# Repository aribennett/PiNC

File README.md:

# PiNC
Open Source Raspberry Pi CNC Control Hardware

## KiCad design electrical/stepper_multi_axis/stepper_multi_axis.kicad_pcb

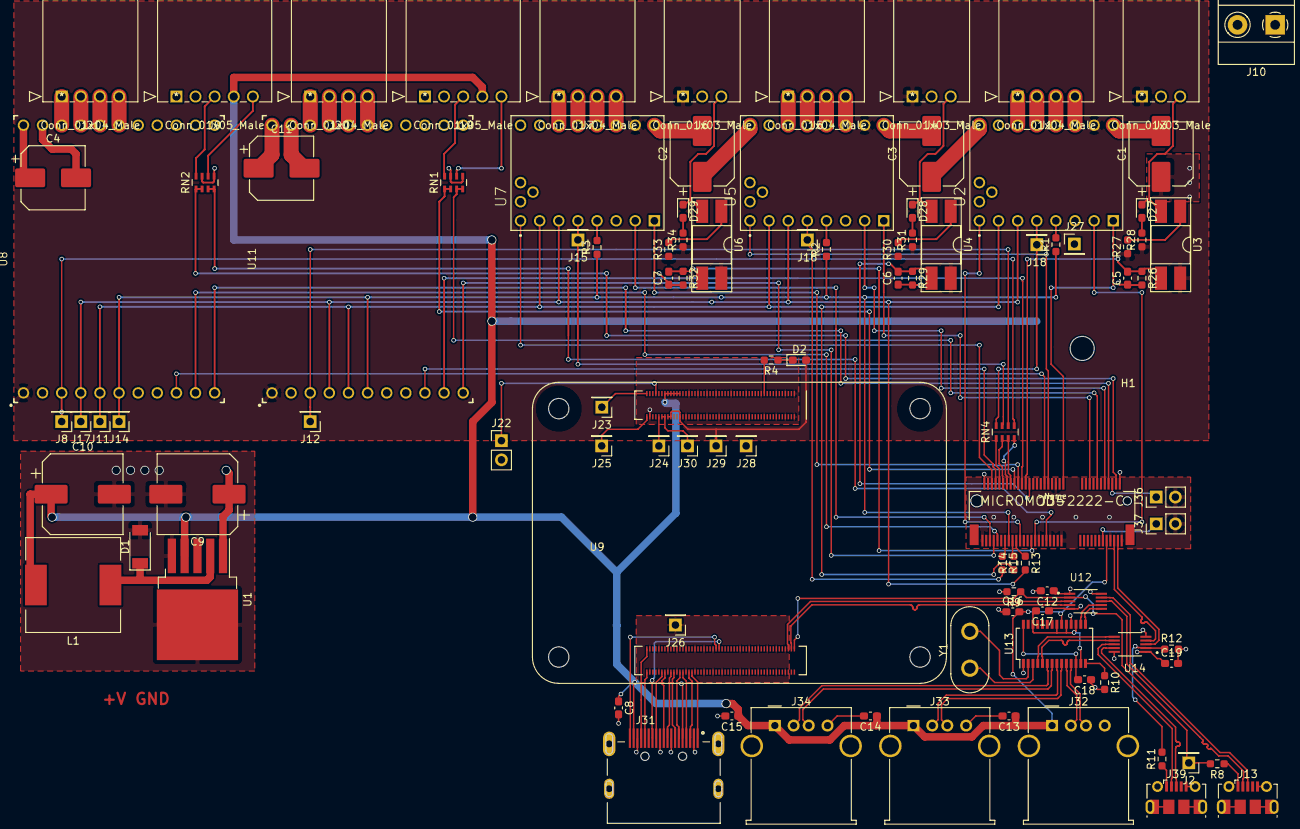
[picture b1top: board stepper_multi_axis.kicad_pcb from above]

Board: 4 copper layers, 102 parts (0 on the bottom side), 126 nets.

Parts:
C1, C2, C3, C4, C11: 10uF; CP_Elec_8x6.7
C5, C6, C7, C8, C12, C13, C14, C15, C19: 100nF; C_0603_1608Metric_Pad1.08x0.95mm_HandSolder
C9: 100uF; CP_Elec_10x12.5
C10: 1000uF; CP_Elec_10x12.5
C16, C17, C18: 10uF; C_0603_1608Metric_Pad1.08x0.95mm_HandSolder
D1: D_Schottky; D_SOD-128
D2: LED; D_0603_1608Metric_Pad1.05x0.95mm_HandSolder
D27, D28, D29: LED; LED_0603_1608Metric_Pad1.05x0.95mm_HandSolder
H1: MountingHole; MountingHole_3.2mm_M3
J1, J5, J7, J20, J21: Conn_01x04_Male; 1719740104
J2, J23, J24, J25, J26, J27, J28, J29, J30: Conn_01x01; PinHeader_1x01_P2.54mm_Vertical
J3, J4, J6: Conn_01x03_Male; 1719740103
J8, J11, J12, J14, J15, J16, J17, J18: Conn_01x01_Male; PinHeader_1x01_P2.54mm_Vertical
J9, J19: Conn_01x05_Male; 1719740105
J10: Conn_01x02_Male; TerminalBlock_Phoenix_MKDS-1,5-2_1x02_P5.00mm_Horizontal
J13, J39: USB_B_Micro; USB_Micro-B_Molex-105017-0001
J22, J36, J37: Conn_01x02_Male; PinHeader_1x02_P2.54mm_Vertical
J31: HDMI_A_1.4; TE_1827059-3
J32, J33, J34: USB_A; USB_A_Molex_67643_Horizontal
J35: MICROMOD-2222-C; M.2-CONNECTOR-E
L1: 100uH; L_12x12mm_H8mm
R1, R2, R3, R13, R14, R15, R26, R27, R28, R29, R30, R31, R32, R33, R34: 100; R_0603_1608Metric_Pad0.98x0.95mm_HandSolder
R4: 1k; R_0603_1608Metric_Pad0.98x0.95mm_HandSolder
R8, R9, R11, R12: 2.2k; R_0603_1608Metric_Pad0.98x0.95mm_HandSolder
R10: 2.7k; R_0603_1608Metric_Pad0.98x0.95mm_HandSolder
RN1, RN2: R_1K_4; R_Array_Concave_4x0603
RN4: R_100_4; R_Array_Concave_4x0603
U1: LM2576S-5; TO-263-5_TabPin3
U2, U5, U7: TMC5160_SILENTSTEPSTICK; MODULE_TMC_SILENTSTEPSTICK
U3, U4, U6: LTV-817; DIP-4_W8.89mm_SMDSocket_LongPads
U8, U11: TMC5160-BOB; 22pin1,5x1,1-BOB
U9: Compute_Module_4_Connectors; Raspberry-Pi-4-Compute-Module
U12, U14: FSUSB42MUX; SOP50P490X110-10N
U13: FE1.1s; SSOP-28_3.9x9.9mm_P0.635mm
Y1: Crystal; Crystal_HC50_Vertical

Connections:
+1V8: J30.1, U9.88, U9.90
+3.3VA: C12.1, C19.1, D2.2, J3.1, J4.1, J6.1, J29.1, J35.2, J35.74, R27.1, R28.1, R30.1, R31.1, R33.1, R34.1, U2.JP2_7, U3.4, U4.4, U5.JP2_7, U6.4, U7.JP2_7, U8.1, U9.78, U9.84, U9.86, U11.1, U12.1, U13.18, U14.1
+5V: C8.1, C10.1, C13.1, C14.1, C15.1, C16.2, J9.4, J19.4, J31.18, J32.1, J33.1, J34.1, J35.9, L1.2, U1.4, U9.77, U9.79, U9.81, U9.83, U9.85, U9.87, U13.20
/CS_A: J12.1, RN4.6, U11.3
/CS_B: J8.1, RN4.5, U8.3
/CS_X: J18.1, RN4.8, U2.JP1_5
/CS_Y: J16.1, R15.2, U5.JP1_5
/CS_Z: J15.1, RN4.7, U7.JP1_5
/D_A: J35.69, U11.11
/D_B: J35.8, U8.11
/ENCA_A: J35.58, RN1.1, RN1.2
/ENCA_B: J35.4, RN2.1, RN2.2
/ENCB_A: J35.14, RN1.3, RN1.4
/ENCB_B: J35.41, RN2.3, RN2.4
/EN_A: J35.68, U11.9
/EN_B: J35.42, U8.9
/LIM_Z: C7.2, J35.49, R32.1, U6.3
/MISO: J14.1, J35.61, R1.1, R2.1, R3.1, U8.6, U11.6
/MOSI: J11.1, R14.1, U2.JP1_7, U5.JP1_7, U7.JP1_7, U8.5, U11.5
/SCK: J17.1, R13.2, U2.JP1_6, U5.JP1_6, U7.JP1_6, U8.4, U11.4
/ST_A: J35.54, U11.10
/ST_B: J35.67, U8.10
/Sheet613FBD85/HDMI0_CEC: J31.13, U9.151
/Sheet613FBD85/HDMI0_CK+: J31.10, U9.188
/Sheet613FBD85/HDMI0_CK-: J31.12, U9.190
/Sheet613FBD85/HDMI0_D0+: J31.7, U9.182
/Sheet613FBD85/HDMI0_D0-: J31.9, U9.184
/Sheet613FBD85/HDMI0_D1+: J31.4, U9.176
/Sheet613FBD85/HDMI0_D1-: J31.6, U9.178
/Sheet613FBD85/HDMI0_D2+: J31.1, U9.170
/Sheet613FBD85/HDMI0_D2-: J31.3, U9.172
/Sheet613FBD85/HDMI0_HOTPLUG: J31.19, U9.153
/Sheet613FBD85/HDMI0_SCL: J31.15, U9.200
/Sheet613FBD85/HDMI0_SDA: J31.16, U9.199
/Sheet613FBD85/USB_N: U9.103, U12.4
/Sheet613FBD85/USB_OTG: J2.1, R8.2, R9.1, U9.101, U12.2
/Sheet613FBD85/USB_P: U9.105, U12.3
/Sheet614CFDB6/1+: J32.3, U13.11
/Sheet614CFDB6/1-: J32.2, U13.10
/Sheet614CFDB6/2+: J33.3, U13.9
/Sheet614CFDB6/2-: J33.2, U13.8
/Sheet614CFDB6/3+: J34.3, U13.7
/Sheet614CFDB6/3-: J34.2, U13.6
/Sheet614CFDB6/INT+: U13.5, U14.7
/Sheet614CFDB6/INT-: U13.4, U14.6
/Sheet614CFDB6/OVERRIDE+: J39.3, U14.9
/Sheet614CFDB6/OVERRIDE-: J39.2, U14.8
/Sheet614CFDB6/PROG+: J13.3, U12.9
/Sheet614CFDB6/PROG-: J13.2, U12.8
/Sheet614CFDB6/USB_A+: U12.7, U13.16
/Sheet614CFDB6/USB_A-: U12.6, U13.15
/Sheet614CFDB6/USB_INTERNAL_N: J35.5, U14.4
/Sheet614CFDB6/USB_INTERNAL_P: J35.3, U14.3
/Stepper_Driver_X/DIR: J35.32, U2.JP1_1
/Stepper_Driver_X/EN: J35.55, U2.JP1_8
/Stepper_Driver_X/Limit: C5.2, J35.52, R26.1, U3.3
/Stepper_Driver_X/STEP: J35.47, U2.JP1_2
/sheet608DFF62/DIR: J35.18, U5.JP1_1
/sheet608DFF62/EN: J35.40, U5.JP1_8
/sheet608DFF62/Limit: C6.2, J35.50, R29.1, U4.3
/sheet608DFF62/STEP: J35.10, U5.JP1_2
/sheet608FE262/DIR: J35.56, U7.JP1_1
/sheet608FE262/EN: J35.70, U7.JP1_8
/sheet608FE262/STEP: J35.71, U7.JP1_2
GND: C1.2, C2.2, C3.2, C4.2, C5.1, C6.1, C7.1, C8.2, C9.2, C10.2, C11.2, C12.2, C13.2, C14.2, C15.2, C16.1, C17.1, C18.1, C19.2, D1.2, J3.2, J4.2, J6.2, J9.1, J10.2, J13.5, J13.6, J19.1, J22.2, J26.1, J27.1, J28.1, J31.2, J31.5, J31.8, J31.11, J31.17, J32.4, J32.5, J33.4, J33.5, J34.4, J34.5, J35.1, J35.7, J35.33, J35.36, J35.39, J35.45, J35.75, J36.2, J37.2, J39.5, J39.6, R9.2, R10.2, R12.2, R26.2, R29.2, R32.2, RN1.5, RN1.7, RN2.5, RN2.7, U1.3, U1.5, U2.JP2_2, U2.JP2_8, U5.JP2_2, U5.JP2_8, U7.JP2_2, U7.JP2_8, U8.2, U8.7, U8.13, U8.18, U9.1, U9.2, U9.7, U9.8, U9.13, U9.14, U9.22, U9.23, U9.32, U9.33, U9.42, U9.43, U9.52, U9.53, U9.59, U9.60, U9.65, U9.66, U9.71, U9.74, U9.98, U9.107, U9.108, U9.113, U9.114, U9.119, U9.120, U9.125, U9.126, U9.131, U9.132, U9.137, U9.138, U9.144, U9.150, U9.155, U9.156, U9.161, U9.162, U9.167, U9.168, U9.173, U9.174, U9.179, U9.180, U9.185, U9.186, U9.191, U9.192, U9.197, U9.198, U11.2, U11.7, U11.13, U11.18, U12.5, U12.10, U13.1, U14.5, U14.10
unnamed: C17.2, U13.13, U13.17, U13.19, U13.21, U13.26
unnamed: C18.2, U13.12, U13.28
unnamed: D1.1, L1.1, U1.2
unnamed: D2.1, R4.1
unnamed: D27.1, J3.3, U3.2
unnamed: D27.2, R28.2
unnamed: D28.1, J4.3, U4.2
unnamed: D28.2, R31.2
unnamed: D29.1, J6.3, U6.2
unnamed: D29.2, R34.2
unnamed: J1.1, U2.JP2_3
unnamed: J1.2, U2.JP2_4
unnamed: J1.3, U2.JP2_5
unnamed: J1.4, U2.JP2_6
unnamed: J5.1, U5.JP2_3
unnamed: J5.2, U5.JP2_4
unnamed: J5.3, U5.JP2_5
unnamed: J5.4, U5.JP2_6
unnamed: J7.1, U7.JP2_3
unnamed: J7.2, U7.JP2_4
unnamed: J7.3, U7.JP2_5
unnamed: J7.4, U7.JP2_6
unnamed: J9.3, RN2.8
unnamed: J9.5, RN2.6
unnamed: J13.1, R8.1
unnamed: J19.3, RN1.8
unnamed: J19.5, RN1.6
unnamed: J20.1, U11.14
unnamed: J20.2, U11.15
unnamed: J20.3, U11.16
unnamed: J20.4, U11.17
unnamed: J21.1, U8.14
unnamed: J21.2, U8.15
unnamed: J21.3, U8.16
unnamed: J21.4, U8.17
unnamed: J22.1, U9.93
unnamed: J23.1, U9.99
unnamed: J24.1, U9.92
unnamed: J25.1, U9.100
unnamed: J35.6, J36.1
unnamed: J35.11, J37.1
unnamed: J35.57, R13.1
unnamed: J35.59, R14.2
unnamed: J35.60, RN4.3
unnamed: J35.62, RN4.4
unnamed: J35.63, R15.1
unnamed: J35.64, RN4.2
unnamed: J35.66, RN4.1
unnamed: J39.1, R11.1
unnamed: R1.2, U2.JP1_4
unnamed: R2.2, U5.JP1_4
unnamed: R3.2, U7.JP1_4
unnamed: R4.2, U9.21
unnamed: R10.1, U13.14
unnamed: R11.2, R12.1, U14.2
unnamed: R27.2, U3.1
unnamed: R30.2, U4.1
unnamed: R33.2, U6.1
unnamed: U13.2, Y1.2
unnamed: U13.3, Y1.1
VBUS: C1.1, C2.1, C3.1, C4.1, C9.1, C11.1, J10.1, U1.1, U2.JP2_1, U5.JP2_1, U7.JP2_1, U8.12, U11.12

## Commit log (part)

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2021-07-29 added cad and folder structure
2021-08-14 added a bunch of kicad stuff
2021-08-16 initial python interface
2021-08-16 updated gitignore
2021-08-16 initial pass at serial packets!
2021-08-16 it makes circles
2021-08-17 added timing to test on rpi
2021-08-18 functioning 4khz hid link
2021-08-19 herp derp
2021-08-19 different IO
2021-08-20 slowed down hid
2021-08-20 added platform agnostic interface
2021-08-20 weird stagning
2021-08-21 mechanical changes
2021-08-23 added higher current drivers
2021-08-30 shipped things
2021-09-01 changed serial framework
2021-09-01 made some changes?
2021-09-02 moved stuff, updated protocol
2021-09-09 finished turret added servo and pwm
2021-09-10 pre delete thru hole
2021-09-12 trying new stuff
2021-09-12 Xometry order 091221
2021-09-29 bunches of changes
2021-09-29 all motors working
2021-09-29 corrected axzes
2021-10-12 added errors and shit
2021-10-12 added gcode solver
2021-10-13 added enable command
2021-10-13 added enable call
2021-10-13 gcoooode
2021-11-15 extracted config
2021-11-19 wiped out lower derivatives
2021-11-19 adde laser, still working.
2021-11-19 rename, add exposure reconfigure
2021-11-20 added a state machine
2021-11-20 calibrated laser
2021-11-20 running gcode!
2021-11-22 cleaned stages
2021-11-29 changed size, we shall see
2021-11-29 expanded firmware
2021-11-29 added solid bodies
2021-11-29 changed packet size to 128
2021-11-29 added counting
2021-11-29 slowed rapid
2021-12-18 fixed turret
2021-12-18 Initial PlatformIO config
2021-12-18 added second project
2021-12-18 removed old libs
2021-12-18 ported to mac
2021-12-18 added jerk control
2021-12-19 mac turret lives
2021-12-19 turret is mostly complete
2021-12-19 removed debug stuff
2021-12-19 added a board ID to the usb devices
2021-12-19 fixed motor command with board ID
2021-12-20 added single axis project
2021-12-21 added terminals
2021-12-23 more requirements
2021-12-23 killed tracking, added cmdline arg
2021-12-23 print the state
2021-12-23 check if controller is working
2021-12-23 added motor command call
2021-12-24 changed init
2021-12-24 re-enable tracking
2021-12-25 Updated z2
2022-01-03 semi-functioning. going to change the planner
2022-02-04 more sw
2022-02-05 added some path planning, killed homing routine
2022-02-05 moar
2022-02-05 homing reneabled
2022-02-05 back to manual
2022-02-05 working servo
2022-02-06 encoders now
2022-02-06 opped jog rate
2022-02-06 fixed jog rate
2022-02-06 lowered deadband
2022-02-06 removed imshow
2022-02-06 changed moments
2022-02-19 updated fw
2022-02-19 updated rule
2022-02-19 updated rules
2022-02-19 i hate udev logic man
2022-02-19 fixed spelling
2022-02-19 changed to symlink
2022-02-19 swapped rule order
2022-02-19 added path to symlink
2022-02-19 added kernel number!
2022-02-19 working udev, tuned controller
2022-02-19 new robot interface
2022-02-19 added trash
2022-02-19 updated packets
2022-02-19 print all the motors
2022-02-19 fixed indexes
2022-02-19 changed control scheme
2022-02-19 oops
2022-02-19 added proportional control
2022-02-19 added a floor handling case
2022-02-19 fixyfix
2022-02-20 added servo position from encoder
2022-02-20 re-add homing
2022-02-20 added a homing speed
2022-02-20 added stall detection
2022-02-20 added new start
2022-02-20 added a print?
2022-02-20 fix the timeout?
2022-02-20 blargh
2022-02-20 idk man
2022-02-20 her derp
2022-02-20 enabled manualstate
2022-02-20 added safe re-enable
2022-02-20 fixed issue with null pointer death
2022-02-20 kinda borken
2022-02-20 re-enable home
2022-02-20 re-enable logging
2022-02-20 added delay. dont love it
2022-02-20 added longer timeout
2022-02-20 added home thing
2022-02-20 reverse reverse
2022-02-20 homing is back babee
2022-02-20 update home strategy
2022-02-20 pulled down timeout
2022-02-20 testing jerg
2022-02-20 adding jog
2022-02-20 drop to manual
2022-02-21 added z jog?
2022-02-21 different logging
2022-02-21 buggos
2022-02-21 printing nominal
2022-02-21 something broken
2022-02-21 found it ...
2022-02-21 big moves
2022-02-21 trimmed laser file
2022-02-21 fix dabug
2022-02-21 added tracking loop and zhoming
2022-02-21 added home center state
2022-02-21 shwoops
2022-02-21 added second jerg
2022-02-21 fixed?
2022-02-21 added another homing pass
2022-02-21 homing should work again
2022-02-21 test motor 0
2022-02-21 remove homing for hot second
2022-02-21 test second axis
2022-02-21 homing should be fully online
2022-02-21 added fix to homing
2022-02-21 fixed home change prant
2022-02-21 changed home posititions
2022-02-21 move more
2022-02-21 tooooo far
2022-02-26 back to homing
2022-03-01 added adc reporting
2022-03-01 update packet def
2022-03-01 added sensor unpacking
2022-03-01 debug them sensors!
2022-03-01 whee
2022-03-01 added output controlls
2022-03-01 added laser config lets goooo
2022-03-01 added laser on off
2022-03-01 changed initail condition
2022-03-01 added fan
2022-03-01 added blower fan to test
2022-03-01 test hotend
2022-03-06 fannnnns
2022-03-06 added pwm output
2022-03-06 test single gpios
2022-03-06 added pwm
2022-03-06 added software pwm, put back in commands
2022-03-06 fixed init maybe
2022-03-06 revert to hardware pwm. no cycles for software
2022-03-06 added thermistor
2022-03-06 voltages backwards
2022-03-06 oooops
2022-03-06 added temp interp
2022-03-06 needs to be monotonically increasing I guess
2022-03-06 whooooopsity poops
2022-03-06 added closed loop thermals
2022-03-06 added index
2022-03-06 whoops need to packl the packet
2022-03-06 wheeee
2022-03-06 wheeeee
2022-03-06 herp derp derp
2022-03-06 try enable lol
2022-04-03 testing
2022-04-03 wider
2022-04-03 busted mask?
2022-04-03 fix it?
2022-04-03 dimmer?
2022-04-03 back to thermistor
2022-04-19 show laser image
2022-04-19 removed bad debug
2022-05-06 lets jog to 00
2022-05-06 lets see if it works
2022-05-06 removed actual motion
2022-05-06 super low kp
2022-05-06 it werk
2022-05-06 disable vleocit controll
2022-05-06 need to enable motor
2022-05-06 disable traking
2022-05-06 added extruder
2022-05-06 reverse and slow doen extruder
2022-05-06 added thermistor controll
2022-05-06 wheee
2022-05-06 I think that might help?
2022-05-06 disable pcf
2022-05-06 added heating step
2022-05-06 fixed stupid reset
2022-05-06 added homing
2022-05-06 added homing and z
2022-05-06 re-enable laser tracking
2022-05-06 maybe?
2022-05-06 maybe maybe?
2022-05-06 added stop condition
2022-05-06 added fine_zHome
2022-05-06 whoops
2022-05-06 fixed start issue
2022-05-06 adjust home
2022-05-06 wrong way
2022-05-06 finer fine home
2022-05-06 getting there
2022-05-06 lets see
2022-05-06 sign issues
2022-05-06 last try
2022-05-06 mayber?
2022-05-06 slow it all down
2022-05-06 changed temp
2022-05-06 moar power
2022-05-10 just homing
2022-05-10 swapped motor
2022-05-10 wrong direction
2022-05-10 added abs stall detection
2022-05-10 why busted
2022-05-10 added print
2022-05-10 maybe fixed?
2022-05-10 welp
2022-05-10 fixed
2022-05-10 shwoop
2022-05-10 fixed scale issue
2022-05-10 change units?
2022-05-10 busted?
2022-05-10 blep
2022-05-10 fixed inversion
2022-05-10 ecentuaLL
2022-05-10 ALL together now
2022-05-10 new gcode
2022-05-10 fixed eof error
2022-05-10 missed subscript
2022-05-10 fixed gcode boog
2022-05-10 minor tweak
2022-05-10 fix edge condition
2022-05-10 welp lets gooo
2022-05-10 added bed on off
2022-05-11 added second thermistor
2022-05-11 maybe table bad?
2022-05-13 turret complete
2022-05-14 finished turret
2022-05-20 removed some files
2022-05-27 lets goooo
2022-05-28 changed gcode
2022-05-28 we'll seeeee
2022-05-29 fix nots
2022-05-29 claener
2022-05-29 cleanup!
2022-06-01 make laser tracking thresh higher
2022-06-02 added test gcode
2022-06-02 blargh need to fix the laser shit
2022-06-02 why u busted
2022-06-02 added benchy
2022-06-02 unstable yo
2022-06-02 slowly increase kp
2022-06-02 huzzah
2022-06-02 why bust
2022-06-02 tweak adn tune
2022-06-02 better pls
2022-06-02 darn
2022-06-02 mabe
2022-06-02 slowdown
2022-06-02 ugh freaking corexy
2022-06-02 blergh
2022-06-02 fix transform
2022-06-02 better debug
2022-06-02 start sloooo
2022-06-02 why u go unstable
2022-06-02 lets gooo
2022-06-06 change to monochrom
2022-06-06 filter
2022-06-06 added depth
2022-06-06 added file writing
2022-06-06 freaking busted
2022-06-06 I wish this worked better
2022-06-06 im dum
2022-06-06 grayscale
2022-06-06 remove non-red channels
2022-06-06 filteeeer
2022-06-06 print out red
2022-06-06 filter better
2022-06-06 whoosp
2022-06-06 more sate
2022-06-06 why does this suk
2022-06-06 higher threhold
2022-06-06 why u suk
2022-06-06 lower thresh
2022-06-06 dumb
2022-06-06 whyyy
2022-06-06 i think I am an idiot
2022-06-06 dunno why
2022-06-06 tunez
2022-06-06 tune z
2022-06-06 added sphere
2022-06-08 brighter laser
2022-06-08 better Z
2022-06-08 lets do a benchy!
2022-06-08 fix z
2022-06-08 hmmm
2022-06-26 added print debug
2022-06-26 changed packet to make faster
2022-06-26 does it work?
2022-06-26 whheee
2022-06-26 disable nominal z
2022-06-26 revert
2022-06-26 added blower and different gcode
2022-06-26 added cooling fan
2022-06-26 added turning on cooling fan later
2022-07-04 okay maybe dis work
2022-07-05 added minibenchy
2022-07-05 no thermal runaway pls
2022-07-17 better benchy
2022-07-17 added chdir
2022-07-17 added test UI file
2022-07-17 test full screen UI
2022-07-18 jotl
2022-07-18 added sw trial
2022-07-18 updated gcode
2022-08-21 added more z
2022-08-21 lets go benchy
2022-08-21 ooops
2022-08-27 changed offset
2022-08-27 added demo computer mount
2022-08-27 new print
2022-08-27 adjust z, add new mount
2022-09-25 is busted?
2022-09-25 whhyyyy
2022-09-25 looks like this did not help
2022-09-25 woop
2022-09-25 added pressure advance
2022-09-25 back to benchy

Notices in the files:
parts and their libraries:
Copyright 2021 Accelerated Designs. All rights reserved.
